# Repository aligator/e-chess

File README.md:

# E-Chess

# MOVED to https://codeberg.org/aligator/e-chess

This project is a physical chess board that is connected to an online chess
server (currently lichess).\
It allows to play chess on a physical board with a computer/remote opponent.

It is currently **WIP** so no full documentation and information is available
yet.\
However there exists already a working prototype including:

- ESP32-S3 Rust firmware
- Android app
- connection to lichess (to lichess via the android app using BLE - web on the
  esp32s3 was too unstable and slow)
- LEDs in the board to show the current game state
- 3d printable OpenSCAD file
- KiCAD electronics schematic

## Future plans

- more gameplay features
- ble over secure connection (currently unencrypted!)
- more easy hardware design (maybe PCB for the whole board?)
- Documentation
- ...

## AI Disclaimer

Yes, I use some AI for this project (especially for the Android app, since I am
not that interested in writing apps...), but the code-architecture, most
firmware code, scad, electronics and the overall design is my own.

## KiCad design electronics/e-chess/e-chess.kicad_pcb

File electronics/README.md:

# E-Chess Electronics

This contains the schematic for the chess board.  
It is designed for an ESP32-S3 development board.  

Currently it is wired completely manually. Therefore it does not contain a PCB yet.

## LEDs

The schematic contains one single LED as placeholder for all 64 WS2812 LEDs.  
They are routed in a snake pattern from the top right to the bottom right.
```
┌💡─💡─💡─💡─💡─💡─💡─💡 <- START
└💡─💡─💡─💡─💡─💡─💡─💡┐
┌💡─💡─💡─💡─💡─💡─💡─💡┘
└💡─💡─💡─💡─💡─💡─💡─💡┐
┌💡─💡─💡─💡─💡─💡─💡─💡┘
└💡─💡─💡─💡─💡─💡─💡─💡┐
┌💡─💡─💡─💡─💡─💡─💡─💡┘
└💡─💡─💡─💡─💡─💡─💡─💡 -> END
``` 

## Reed sensors

For the Reed sensors a matrix with simple reed contacts is used.  
It resembles the matrix described [here](https://www-user.tu-chemnitz.de/~heha/Mikrocontroller/Tastenmatrix.htm).

The IO expander MCP23017 is used to connect the columns and rows.  
As it has exactly 16 pins, it matches exactly the required 8x8 matrix.

The MCP23017 has built in pull-up resistors, so no external resistors are needed.

GPB (pin 0 - 7) is used as output for the columns.  
GPA (pin 21 - 28) is used as input for the rows.  

The matrix resembles the actual chess board starting with A1 at the bottom left.  
So A1 == GPB0|GPA0, A2 == GPB1|GPA0, ... H8 == GPB7|GPA7.

To read the status, the firmware will set all rows but one to high and then read the columns.  
Then it will do the same for the next row.  

## Power supply

The ESP32-S3 is powered by the USB-C connector.  

* Since the esp works with 3.3V, the IO expander is also running on 3.3V.  
* Since the LEDs are WS2812B, they need 5V, coming from the ESP dev board. 
 **You may need to connect the IN-OUT jumper on the ESP dev board to receive 5V on the 5V-pin.**

For now my plan is to avoid driving the LEDS with full power.  
I try to handle everything with 500 mA. However this may need to be changed later.

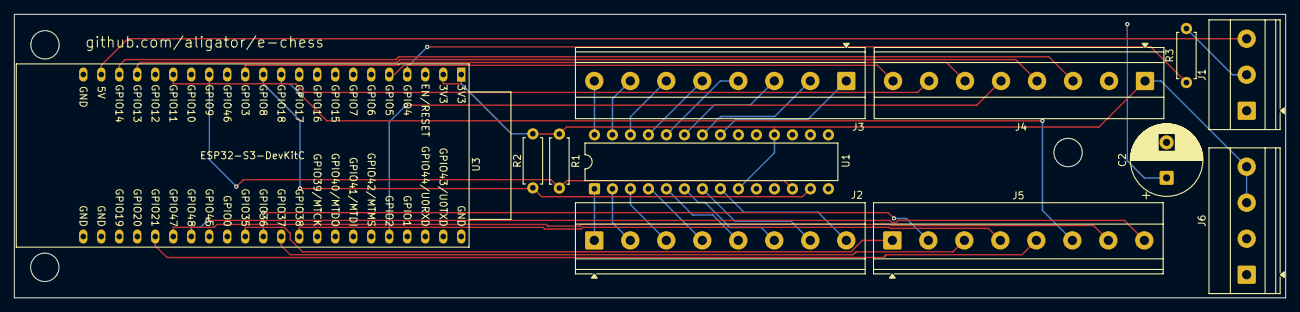
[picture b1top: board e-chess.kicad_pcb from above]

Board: 2 copper layers, 179.4 x 40.0 mm, 15 parts (0 on the bottom side), 37 nets.

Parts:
C2: 470 µF; CP_Radial_D10.0mm_P5.00mm
J1: WS2812_LEDs; TerminalBlock_Phoenix_MKDS-1,5-3-5.08_1x03_P5.08mm_Horizont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
J2: Outputs; TerminalBlock_Phoenix_MKDS-1,5-8-5.08_1x08_P5.08mm_Horizont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
J3: Inputs; TerminalBlock_Phoenix_MKDS-1,5-8-5.08_1x08_P5.08mm_Horizont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
J4: e-Paper 1.54 inch; TerminalBlock_Phoenix_MKDS-1,5-8-5.08_1x08_P5.08mm_Horizont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
J5: Arbitary I/O; TerminalBlock_Phoenix_MKDS-1,5-8-5.08_1x08_P5.08mm_Horizont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
J6: Power for I/O; TerminalBlock_Phoenix_MKDS-1,5-4-5.08_1x04_P5.08mm_Horizont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
R1, R2: R4.7k; R_Axial_DIN0207_L6.3mm_D2.5mm_P7.62mm_Horizontal
R3: R470; R_Axial_DIN0207_L6.3mm_D2.5mm_P7.62mm_Horizontal
REF00, REF01, REF02: MountingHole_4mm
U1: MCP23017_SP; DIP-28_W7.62mm
U3: ESP32-S3-DevKitC

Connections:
+3.3V: J4.1 (VCC), J6.3 (3V3), J6.4 (3V3), R1.2, R2.2, U1.9 (VDD), U1.18 (~RESET), U3.1 (3V3), U3.2 (3V3)
+5V: C2.1, J1.3 (VDD), U3.21 (5V)
GND: C2.2, J1.1 (GND), J4.2 (GND), J6.1 (GND), J6.2 (GND), U1.10 (VSS), U1.15 (A0), U1.16 (A1), U1.17 (A2), U3.22 (GND), U3.23 (GND), U3.24 (GND), U3.44 (GND)
unnamed: J1.2 (DIN), R3.2
unnamed: J2.1, U1.1 (GPB0)
unnamed: J2.2, U1.2 (GPB1)
unnamed: J2.3, U1.3 (GPB2)
unnamed: J2.4, U1.4 (GPB3)
unnamed: J2.5, U1.5 (GPB4)
unnamed: J2.6, U1.6 (GPB5)
unnamed: J2.7, U1.7 (GPB6)
unnamed: J2.8, U1.8 (GPB7)
unnamed: J3.1, U1.21 (GPA0)
unnamed: J3.2, U1.22 (GPA1)
unnamed: J3.3, U1.23 (GPA2)
unnamed: J3.4, U1.24 (GPA3)
unnamed: J3.5, U1.25 (GPA4)
unnamed: J3.6, U1.26 (GPA5)
unnamed: J3.7, U1.27 (GPA6)
unnamed: J3.8, U1.28 (GPA7)
unnamed: J4.8 (BUSY), U3.5 (GPIO5/ADC1_CH4)
unnamed: J4.4 (CLK), U3.19 (GPIO13/ADC2_CH2)
unnamed: J4.5 (CS), U3.40 (GPIO2/ADC1_CH1)
unnamed: J4.6 (DC), U3.13 (GPIO3/ADC1_CH2)
unnamed: J4.3 (DIN), U3.20 (GPIO14/ADC2_CH3)
unnamed: J4.7 (RST), U3.17 (GPIO11/ADC2_CH0)
unnamed: J5.6 (GPIO18), U3.11 (GPIO18/ADC2_CH7)
unnamed: J5.5 (GPIO21), U3.27 (GPIO21)
unnamed: J5.1 (GPIO35), U3.32 (GPIO35)
unnamed: J5.2 (GPIO36), U3.33 (GPIO36)
unnamed: J5.3 (GPIO37), U3.34 (GPIO37)
unnamed: J5.4 (GPIO38), U3.35 (GPIO38)
unnamed: J5.7 (GPIO47), U3.28 (GPIO47)
unnamed: J5.8 (GPIO48), U3.29 (GPIO48)
unnamed: R1.1, U1.12 (SCK), U3.15 (GPIO9/ADC1_CH8)
unnamed: R2.1, U1.13 (SDA), U3.12 (GPIO8/ADC1_CH7)
unnamed: R3.1, U3.4 (GPIO4/ADC1_CH3)

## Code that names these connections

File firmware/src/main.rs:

use crate::board::Board;
#[cfg(feature = "no_board")]
use crate::board::FakeBoard;
use crate::event::EventManager;
use crate::game::GameCommandEvent;
use anyhow::Result;
use board::MCP23017Board;
use chess::BitBoard;
use chess_game::game::ChessGameState;
use eink_display::ChessEinkDisplay;
use embedded_hal::spi::SpiDevice;
use esp_idf_hal::gpio::{Gpio0, PinDriver};
use esp_idf_hal::peripherals::Peripherals;
use esp_idf_hal::prelude::*;
use esp_idf_hal::rmt::TxRmtDriver;
use esp_idf_hal::spi::config::DriverConfig;
use esp_idf_hal::spi::{SpiConfig, SpiDeviceDriver, SpiDriver};
use esp_idf_hal::{i2c::*, rmt::config::TransmitConfig};
use game::GameStateEvent;
use log::*;
use std::thread::sleep;
use std::time::Duration;
use ws2812_esp32_rmt_driver::Ws2812Esp32Rmt;

mod bluetooth;
mod board;
mod constants;
mod display;
mod eink_display;
mod event;
mod game;
mod util;

#[derive(Debug, Clone)]
pub enum SetupEvent {
    BLEPin(u32)
}

#[derive(Debug, Clone)]
enum Event {
    GameState(GameStateEvent),
    GameCommand(GameCommandEvent),
    Setup(SetupEvent),
}

unsafe impl Send for Event {}
unsafe impl Sync for Event {}

fn run_game<'a, ButtonA, ButtonB, SPI, BUSY, DC, RST, DELAY>(
    mcp23017: I2cDriver<'_>,
    ws2812: Ws2812Esp32Rmt,
    eink_display: &mut ChessEinkDisplay<ButtonA, ButtonB, SPI, BUSY, DC, RST, DELAY>,
    event_manager: &EventManager<Event>,
) -> Result<()>
where
    ButtonA: embedded_hal::digital::InputPin,
    ButtonB: embedded_hal::digital::InputPin,
    SPI: SpiDevice,
    BUSY: embedded_hal::digital::InputPin,
    DC: embedded_hal::digital::OutputPin,
    RST: embedded_hal::digital::OutputPin,
    DELAY: embedded_hal::delay::DelayNs + 'a,
{
    #[cfg(not(feature = "no_board"))]
    let mut board: Box<dyn Board> = Box::from(MCP23017Board::new(mcp23017, 0x20));
    #[cfg(feature = "no_board")]
    let mut board: Box<dyn Board> = Box::from(FakeBoard {});

    board.setup()?;

    let mut display = display::Display::new(ws2812);
    display.setup()?;

    game::run_game(event_manager);

    // Start the main loop
    info!("Start app loop");

    let rx = event_manager.create_receiver();
    let tx = event_manager.create_sender();
    let mut last_physical = BitBoard::new(0);
    let mut last_game_state: Option<ChessGameState> = None;

    // Always start with a local game (standard chess position)
    let initial_game_id = "rnbqkbnr/pppppppp/8/8/8/8/PPPPPPPP/RNBQKBNR w KQkq - 0 1".to_string();

    tx.send(Event::GameCommand(GameCommandEvent::LoadNewGame {
        game_key: initial_game_id,
    }))?;

    // Start the event manager after setting up everything.
    event_manager.start_thread();
    loop {
        // Tick the physical board
        let physical = board.tick(last_physical)?;
        if physical != last_physical {
            last_physical = physical;
            if let Err(e) = tx.send(Event::GameCommand(GameCommandEvent::UpdatePhysical {
                bitboard: physical,
            })) {
                warn!("Failed to send update physical event: {:?}", e);
            }
        }

        // Check if event happens
        if let Ok(event) = rx.try_recv() {
            match event.clone() {
                Event::GameState(game_state_event) => match game_state_event {
                    GameStateEvent::UpdateGame(game_state) => {
                        info!("Received update game state event: {:?}", game_state);

                        last_game_state = Some(game_state);
                    }
                    _ => {}
                },
                _ => {}
            }
        }

        display.tick(&last_game_state)?;
        eink_display.tick(physical, &last_game_state)?;
    }
}

/// Entry point to our application.
fn main() -> Result<()> {
    // It is necessary to call this function once. Otherwise some patches to the runtime
    // implemented by esp-idf-sys might not link properly. See https://github.com/esp-rs/esp-idf-template/issues/71
    esp_idf_svc::sys::link_patches();

    // Bind the log crate to the ESP Logging facilities
    esp_idf_svc::log::EspLogger::initialize_default();

    let peripherals = Peripherals::take().unwrap();

    info!("Starting E-Chess!");
    #[cfg(esp32)]
    info!("Running on ESP32");
    #[cfg(esp32s3)]
    info!("Running on ESP32S3");

    // Initialize the I2C bus for the MCP23017
    let config = I2cConfig::new().baudrate(100.kHz().into());
    #[cfg(esp32)]
    let mcp23017: I2cDriver<'_> = {
        let sda = peripherals.pins.gpio21;
        let scl = peripherals.pins.gpio22;
        I2cDriver::new(peripherals.i2c0, sda, scl, &config)?
    };
    #[cfg(esp32s3)]
    let mcp23017: I2cDriver<'_> = {
        let sda = peripherals.pins.gpio8;
        let scl = peripherals.pins.gpio9;
        I2cDriver::new(peripherals.i2c0, sda, scl, &config)?
    };

    let driver_config = TransmitConfig::new()
        .clock_divider(1) // Required parameter.
        .mem_block_num(8); // Increase the number depending on your code.

    // Initialize the RMT driver for the WS2812
    #[cfg(esp32)]
    let driver = TxRmtDriver::new(
        peripherals.rmt.channel0,
        peripherals.pins.gpio23,
        &driver_config,
    )?;
    #[cfg(esp32s3)]
    let driver = TxRmtDriver::new(
        peripherals.rmt.channel0,
        peripherals.pins.gpio4,
        &driver_config,
    )?;
    let ws2812 = Ws2812Esp32Rmt::new_with_rmt_driver(driver)?;

    // Initialize the SPI bus for the E-Paper display
    let spi_config = SpiConfig::new()
        .baudrate(Hertz(4_000_000))
        .data_mode(esp_idf_hal::spi::config::MODE_0);
    let driver_config = DriverConfig::new();
    // Create delay provider
    let delay = esp_idf_hal::delay::Ets;
    #[cfg(esp32)]
    let (spi_driver, cs, busy, dc, rst, button_a, button_b) = {
        let spi = peripherals.spi2;
        let sclk = peripherals.pins.gpio18;
        let mosi = peripherals.pins.gpio23;
        let cs = peripherals.pins.gpio5;
        let dc = peripherals.pins.gpio2;
        let busy = peripherals.pins.gpio4;
        let rst = peripherals.pins.gpio0;

        let spi_driver = SpiDriver::new(spi, sclk, mosi, Option::<Gpio0>::None, &driver_config)?;

        let button_a = peripherals.pins.gpio35;
        let button_b = peripherals.pins.gpio36;

        (spi_driver, cs, busy, dc, rst, button_a, button_b)
    };

    #[cfg(esp32s3)]
    let (spi_driver, cs, busy, dc, rst, button_a, button_b) = {
        let spi = peripherals.spi2;
        let sclk = peripherals.pins.gpio13;
        let mosi = peripherals.pins.gpio14;
        let cs = peripherals.pins.gpio2;
        let dc = peripherals.pins.gpio3;
        let busy = peripherals.pins.gpio5;
        let rst = peripherals.pins.gpio11;

        let spi_driver = SpiDriver::new(spi, sclk, mosi, Option::<Gpio0>::None, &driver_config)?;

        let button_a = peripherals.pins.gpio35;
        let button_b = peripherals.pins.gpio36;

        (spi_driver, cs, busy, dc, rst, button_a, button_b)
    };
    let spi = SpiDeviceDriver::new(spi_driver, Some(cs), &spi_config)?;

    // Setup the button pins and enable the internal pullup.
    let mut button_a_driver = PinDriver::input(button_a)?;
    button_a_driver.set_pull(esp_idf_hal::gpio::Pull::Up)?;
    let mut button_b_driver = PinDriver::input(button_b)?;
    button_b_driver.set_pull(esp_idf_hal::gpio::Pull::Up)?;

    let event_manager = EventManager::<Event>::new();

    let mut eink_display = eink_display::ChessEinkDisplay::new(
        button_a_driver,
        button_b_driver,
        spi,
        PinDriver::input(busy)?,
        PinDriver::output(dc)?,
        PinDriver::output(rst)?,
        delay,
        None,
        &event_manager,
    )?;

    eink_display.setup()?;

    match run_game(mcp23017, ws2812, &mut eink_display, &event_manager) {
        Ok(_) => {
            warn!("Stopping game loop");
            Ok(())
        }
        Err(e) => {
            warn!("Stopping game loop due to error: {:?}", e);
            loop {
                sleep(Duration::from_millis(1000));
            }
        }
    }
}

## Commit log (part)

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2024-06-23 Init
2024-06-23 Add scad model
2024-06-23 Beginn redesign of the 3d model
2024-06-26 Add grid
2024-06-30 Fix grid rendering
2024-06-30 Add printing tolerance
2024-06-30 Add bottom plate
2024-06-30 Add cutting into 4 parts for smaller printers
2024-07-07 Better default values
2024-07-14 Implement simple firmware for prototype 2 including neopixels
2024-07-14 Use esp32 board
2024-07-14 Restructure project and add a rust firmware
2024-07-14 wlan-example
2024-07-14 experiment with leds
2024-07-16 Implement grid-reading in Rust
2024-07-16 Run logic on core1 which should help later when using wlan.
2024-07-21 Use xTaskCreatePinnedToCore to run on core1
2024-07-21 Cleanup and use pin 23 for led
2024-07-27 Move wifi setup into extra thread on core0
2024-07-27 Move wlan code into own file
2024-07-27 Implement first bits for a TicTacToe board
2024-07-27 Add winning condition
2024-07-28 Fix winning condition
2024-07-28 Implement board history
2024-07-28 Allow to undo a move
2024-07-28 Check if the undo is valid
2024-08-02 Hide led wiring
2024-08-02 Only expose one strip through the wall
2024-08-02 Enable all by default
2024-08-04 Reformat
2024-08-04 Add electronics box with a cover hold by magnets
2024-08-04 Fix cutting
2024-08-04 Add stamps to the cover at the center
2024-08-24 Improve 3d model cutout and tollerance
2024-08-24 Add option to render all as printable at once
2024-08-24 Fix led size
2024-08-24 Fix wire hole
2024-08-25 Improve electronic cover
2024-12-15 Split top into board and grid
2024-12-15 Experiment
2024-12-15 More stable defaults for the top grid
2024-12-15 Cleanup and auto refomrat with a better code style
2024-12-18 Fix top
2024-12-19 Higher top
2024-12-25 Fix top grid height
2024-12-31 bigger bottomWallSize
2025-01-06 Fix wire routing and even bigger bottom wall size
2025-01-09 Move workspace file to root
2025-01-12 Add Reed Pins
2025-01-12 Fix grid and topGrid
2025-01-12 Fix top board sizing
2025-01-12 Fix bottom case size
2025-01-12 Fix reed pins
2025-01-12 Improve reed pins
2025-01-12 Move wires from the grid to the bottom.
2025-01-12 Set correct reed defaults
2025-01-13 Improve wire holes
2025-01-14 Improve electronic layout
2025-01-15 Use espflash
2025-01-15 Add hole for usb cable
2025-01-15 Reduce bridging size in the led strip-cutouts in the walls
2025-01-15 Add option for the top board to be multicolor by adding an extra layer.
    It can be confugured to alternate even or odd, and the additional height can be set (e.g. 0.2mm)
2025-01-15 fix LedStripWiresInWalls for odd board sizes
2025-01-15 Increase reed offset for better detection
2025-01-15 Add workspace for the chess game logic - independent of the micro controller
2025-01-15 Implement taking away pieces
2025-01-15 Test if firmware still compiles
2025-01-15 Use a chess state enum for better state machine handling
2025-01-15 Allow re-putting to the same position
2025-01-15 Show possible moves
2025-01-15 Move workspace to root
2025-01-15 Add a way to attack (take your piece, then take enemy piece)
2025-01-15 Simulate taking and placing physical pieces completely and display wrong ones.
2025-01-16 Reed pins printable without support
2025-01-16 Improve comment
2025-01-16 Implement board for chess
2025-01-16 Remove wrong double cut4 on the reed pins
2025-01-17 First experiment with chess dependency on the esp
2025-02-16 Example to read and write with the io expander
2025-02-16 Implement board with the i2c i/o expander
2025-02-17 Implement Display with the leds
2025-02-18 Fix led mapping
2025-02-22 Experiment wit AP
2025-02-22 Fix board to shift the bits to correct position
2025-02-22 Display possible moves as green
2025-02-23 Connect to wifi
2025-02-23 WIFI connection wizzard
2025-02-23 Reenable other code and make it so that the webserver is started in ap and in client mode
2025-02-23 cleanup
2025-03-01 Improve server creation
    Make it possible to handle the wifi-connect routes separately.
    Now the game specific routes can be created and registered separately.
2025-03-01 Display game state in web
2025-03-01 Style pages
2025-03-01 Add favicon
2025-03-01 Send new pixels only when needed
2025-03-02 Implement settings for api key
2025-03-04 Preserve wifi settings even when starting the AP
2025-03-05 Use own fork of the chess lib
2025-03-05 Begin implementing connector for online mode
2025-03-05 Update firmware code to match chess game changes
2025-03-06 A first test to call the stream game state api with the micro controller
2025-03-06 Begin implementing lichess api
    introduce Request trait, to be able to use the same logic with the esp and the test project using different request implementations
2025-03-07 Start implementing the Lichess Connector
2025-03-08 Move simulator as example
2025-03-08 Implement lichess api
2025-03-08 Fix game processing
2025-03-08 Cleanup debug logs
2025-03-09 Fix error handling for the lib and start implementing the requester for the esp
2025-03-09 Make stream async as it should be and avoid auto-restart on api error to avoid spamming requests
2025-03-09 Wait for dns
2025-03-09 Fix request parsing
2025-03-09 Add todo
2025-03-09 First working POC connecting the physical board to lichess
2025-03-09 Colorize last moved piece
2025-03-09 Fix sending too many post requests
2025-03-09 Improve request handling on esp
2025-03-15 Improve event system
2025-03-15 Create new stream channels
2025-03-15 stream game without full page refresh
2025-03-15 avoid stopping game loop on error
2025-03-15 Fix board streaming
2025-03-15 Improve page styling and handling
2025-03-15 Improve colorizing to also colorize the currently in-move-piece, improve loading indicator
2025-03-15 Improve game loading and simplify web ui
2025-03-15 Improve styling - add menu
2025-03-15 Reduce sleep
2025-03-19 Fix ignoring broken board state.
    Now it should stop any processing of the physical state if more than one piece is "being moved"
2025-03-19 Some code simplifying
2025-03-19 Update ws2812-esp32-rmt-driver to incorporate the new mem block fix to mitigate flickering
2025-03-19 Fix main
2025-03-19 log cleanup
2025-03-24 Some logging in requestl.rs
2025-03-24 Simplify types of the game and connector. Now it is possible to exchange the implementation.
2025-03-24 FW: Allow loading a local game by providing a FEN
2025-04-17 Support if the remote board takes back a step - effectively resets the game for now.
2025-04-17 Load empty local game initially
2025-04-26 Add inner walls on the bottom part to better glue them together if split
2025-04-26 Adapt the grid to split it into 4 slots
2025-04-26 Fix grid and top grid to match properly
2025-04-26 Adapt the topBoard
2025-04-26 Rotate the reed so that is diagonal. This is better because now it is in the shadow of the pin itself - and therefore doesn't cast a new shadow
2025-04-26 Remove cpp playground
2025-04-26 Cut wires into the borders between the slots
2025-04-27 Make initial setup more robust, fix css not served initially
2025-04-27 Add support for esp32 S3
2025-04-27 Select pins based on the board type
2025-04-27 Fix wifi config loading and avoid cfg warning
2025-04-27 Fix initial game loading of a new, local game
2025-05-03 Improve electronic break trhough and usb
2025-05-07 experiment with tscircuit
2025-05-07 Add OTA functionality
2025-05-17 Working eink display connection
2025-05-17 use graphic lib
2025-05-17 Add qr code generator to deplay wifi
2025-05-29 Put game into own thread
2025-06-08 Fix top part
2025-06-15 Support Printing the top with a multicolor printer
2025-06-19 Try out state management with a central eventManager
2025-06-19 simplify multicolor a bit
2025-06-19 Fix wifi
2025-06-19 Sleep thread a bit to avoid blocking the core
2025-06-21 Fix game state sending
2025-06-21 Send and use consistent game state
2025-06-21 make lights a bit brighter
2025-06-21 Add new game button to start a new local game
2025-06-21 Improve api key handling and game loading
2025-06-21 Fix led order docu
2025-06-22 Add link to https://www.instructables.com/Low-Cost-Automation-ESP32-and-16-Relays/
2025-06-22 Improve electronic cutouts to match the new reed location & orientation
2025-10-25 Improve electroinic schmeatics
2025-10-25 Draw PCB
2025-10-25 Remove references to embassy
    As they seem to be broken and let the build fail. Also I think they are not needed for now...
2025-10-25 Include vscode settings
2025-10-25 change exposed pins a bit
2025-10-28 Add more debugging info
2025-10-28 Some version updates
2025-10-28 Make no_board feature working again
2025-10-28 begin work on a simple menu for the e-ink
2025-10-28 unwrap pullup
2025-10-28 Implement displaying the connection info
2025-10-28 Add info page navigation using a button
2025-10-28 Improve wifi reliability by not sleeping
2025-10-28 Wait for ip being available
2025-10-28 Improve e paper pages
2025-10-28 Remove doubele Readme
2025-11-11 Add display cutot to the electronic cover
2025-11-11 Add holes for buttons
2025-11-11 Add border for the electronic cover
2025-11-19 set button hole size to 7
2025-11-22 make display screws a bit bigger
2025-11-22 Place display at the bottom
2025-11-22 Move terminals a bit in to have more space for the cables
2025-11-22 Add pcb 3d model to scad for visualization
2025-11-22 Add screw holes for the pcb
2025-11-22 Improve display positioning
2025-11-22 Add display overlap for a nicer look
2025-11-22 Fix pcb screw
2025-12-21 Implement loading open games in the web ui.
2025-12-21 Make things more stable (ota, only ap connection,...)
2025-12-25 Experiment with BLE
2025-12-26 Add android app
2025-12-26 Add ble permissions to manifest
2025-12-26 list devices
2025-12-26 poc two way communication over ble
2025-12-26 Implement bluetooth with the requester so that it is at a lower level and may be used for REST-Like calls directly. This makes it directly compatible to the current chess implementation
2025-12-26 Try to make the android app work...
2025-12-27 Make it basically work
2025-12-28 Improve ble code
2025-12-30 Improve android app
2025-12-31 Requests over BLE
2026-01-01 Add game loading characteristic to the firmware
2026-01-02 Commit ai app code POC as reference to build a propper bluetooth service
2026-01-02 Start implementing ble connection propperly
2026-01-03 Make scanning working again, adapt ui for the new service structure
2026-01-03 Implement game key loading app-side
2026-01-04 Improve ble code and fix most of it
2026-01-04 Fix streaming a bit more
2026-01-04 Yay it works now!
2026-01-04 Remove settings & cleanup
2026-01-04 Fix game play and take back handling and cleanup
2026-01-04 Fix permissions and load games in ui
2026-01-04 Improve ui by showing loading indicator for game loading and fix some things
2026-01-04 add refresh button for the game list
2026-01-04 Fix translations and refactor configuration with a Configuration store
2026-01-05 Keep screen on, refactor ble api
2026-01-05 Load open games via the api called by the board.
    yes this is a full roundtrip, but it keeps all lichess specific only in
    the firmware...
2026-01-05 Rename bluetooth tabt to chess
2026-01-05 Fix loading indicators
2026-01-05 fix panix in releasemode
2026-01-06 use single thread for ble sending in the firmware
2026-01-06 fix crash in release for now by setting opt-level to z not s.
    No idea why this works...
2026-01-06 Update dependencies
2026-01-06 Refactor Bluetooth in the firmware and split it into multiple handlers. Add OTA
2026-01-07 Simplify firmware update
2026-01-07 theoretically working ota
2026-01-07 implement working ota
2026-01-07 increase MTU
2026-01-07 Improve OTA and UX
2026-01-09 Replace http webserver by a BLE bridge using an android app. This works much more stable.
2026-01-11 Add BLE pin to firmware
2026-01-11 Make BLE bonding basically work
2026-02-06 Add debug logging
2026-02-06 Refactor App
2026-02-07 Add mock mode, game screen and other refactoring
2026-02-08 Fix race condition on setting up ble connection
2026-05-16 Implement loading and thinking indication in online games for better feedback to the user
2026-05-16 Add loosing / winning animation
2026-05-16 Cleanup display code by splitting out the animations
